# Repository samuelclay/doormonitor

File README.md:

remote-door-sensor
==================

Turns a remote light on and off based on the position of a door.

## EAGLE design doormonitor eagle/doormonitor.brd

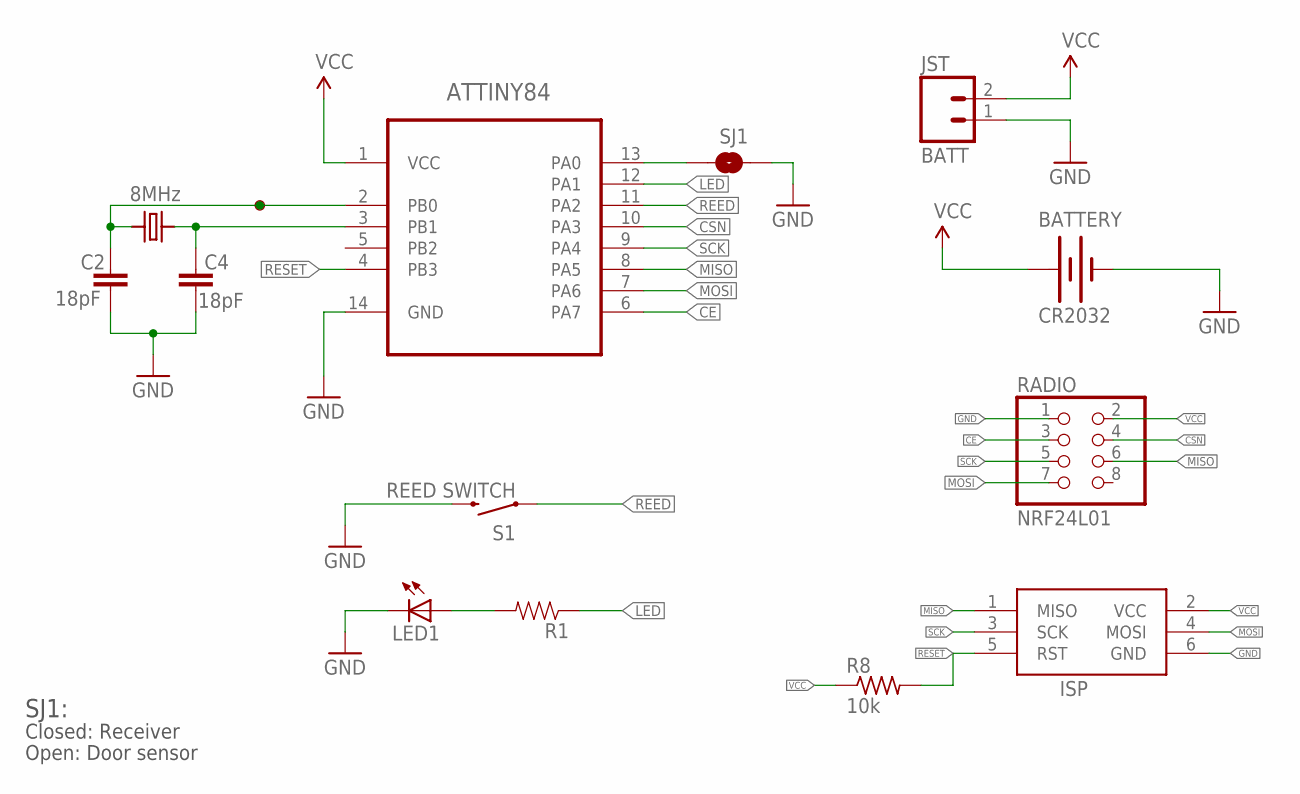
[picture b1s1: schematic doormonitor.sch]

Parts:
ATTINY84: ATTINY84-20SSU; SOIC127P600X175-14N
BATTERY: CR2032; BATTCON_20MM_4LEGS_OVERPASTE
C2, C4: 18pF; 0805
ISP: AVRISP-6; AVRISP
JST: BATT; JST-2-PTH-VERT
LED1: LED5MM
R1: RESISTOR0805-RES; 0805
R8: 10k; R0805
RADIO: NRF24L01; 2X04
S1: REED SWITCH; REED_SWITCH_PTH
SJ1: Receiver?; SJ_2S
U$1: VIA; FANCYVIA
Y1: 8MHz; NX8045GB

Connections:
CE: ATTINY84.6 (PA7), RADIO.3
CSN: ATTINY84.10 (PA3), RADIO.4
GND: ATTINY84.14 (GND), BATTERY.2 (-), C2.2, C4.2, ISP.6 (GND), JST.1, LED1.K (C), RADIO.1, S1.P$2 (2), SJ1.1
LED: ATTINY84.12 (PA1), R1.1
MISO: ATTINY84.8 (PA5), ISP.1 (MISO), RADIO.6
MOSI: ATTINY84.7 (PA6), ISP.4 (MOSI), RADIO.7
unnamed: ATTINY84.13 (PA0), SJ1.2
unnamed: ATTINY84.2 (PB0), C2.1, U$1.VIA, Y1.P$2 (2)
unnamed: ATTINY84.3 (PB1), C4.1, Y1.P$1 (1)
unnamed: LED1.A, R1.2
REED: ATTINY84.11 (PA2), S1.P$1 (1)
RESET: ATTINY84.4 (PB3), ISP.5 (RST), R8.2
SCK: ATTINY84.9 (PA4), ISP.3 (SCK), RADIO.5
VCC: ATTINY84.1 (VCC), BATTERY.1 (+), ISP.2 (VCC), JST.2, R8.1, RADIO.2

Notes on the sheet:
Closed: Receiver
Open: Door sensor
SJ1:

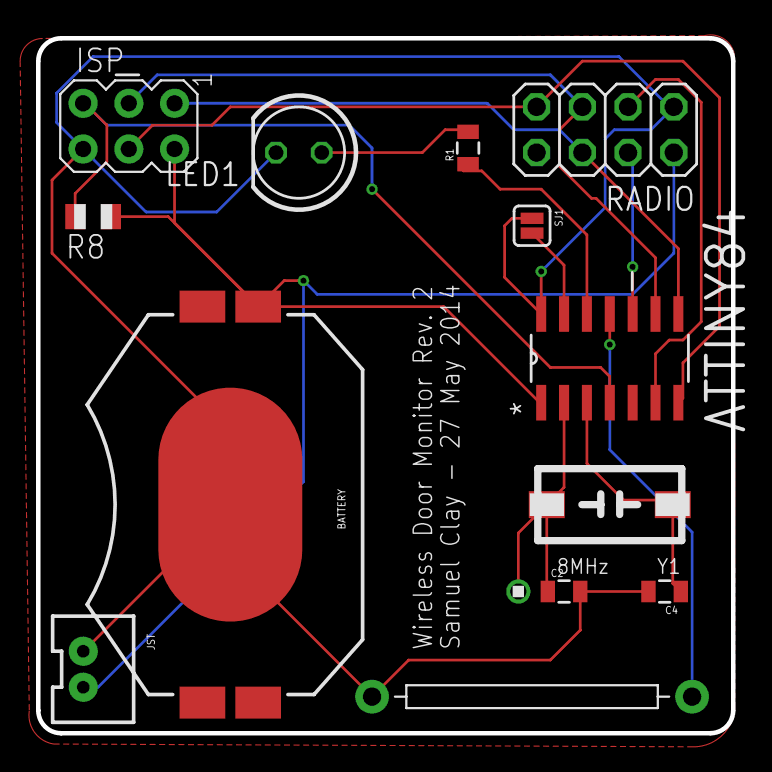
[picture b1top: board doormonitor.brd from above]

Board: 4 copper layers, 38.6 x 38.6 mm, 14 parts (0 on the bottom side), 14 nets.

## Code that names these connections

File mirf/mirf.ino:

/*

This is an attiny84 example code for the nRF24L01 that can communicate with RF24 library

All the support files and libraries for the attiny for nRF24L01 is at repo listed  below

 *  repo   : https://github.com/stanleyseow/arduino-nrf24l01/
 *  Author : Stanley Seow
 *  e-mail : stanleyseow@gmail.com
 *  date   : 8 Aug 2013
 
 Some default values to take note when using this mirf/spi85 library
 Uses Mirf forked library from https://github.com/xdarklight/arduino-nrf24l01
 
 - node addressing is similar to RF24 libs but the bytes are flipped 
 
   byte TADDR[] = {0xe3, 0xf0, 0xf0, 0xf0, 0xf0}; will matches receiver node of RF24 below 
   const uint64_t pipes[2] = { 0x7365727631LL, 0xF0F0F0F0E3LL };
 
 The repo for the RF24 lib is at https://github.com/stanleyseow/RF24/

 Added TinyDebugSerial to the codes for TX only serial debugging
 https://code.google.com/p/arduino-tiny/

*/

#include <SPI85.h>
#include <Mirf.h>
#include <MirfHardwareSpi85Driver.h>
#include <TinyDebugSerial.h>
TinyDebugSerial mySerial = TinyDebugSerial(); // PB0 on attiny84

// This USI was defined in SPI85.cpp
// Not to be confused with SPI (MOSI/MISO) used by ICSP pins
// Refer to page 61 of attiny84 datahseet
//
//#define USI-DO  5
//#define USI-DI  4
//#define USCK   6

#define CE    7    
#define CSN   3 

// ATMEL ATTINY84 / ARDUINO
//
//                           +-\/-+
//                     VCC  1|    |14  GND
//  SerialTx   (D  0)  PB0  2|    |13  AREF (D 10)
//             (D  1)  PB1  3|    |12  PA1  (D  9) 
//  RESET              PB3  4|    |11  PA2  (D  8) 
//  PWM  INT0  (D  2)  PB2  5|    |10  PA3  (D  7)  CE
//  SS/CSN     (D  3)  PA7  6|    |9   PA4  (D  6)  USCK
//  USI-DI     (D  4)  PA6  7|    |8   PA5  (D  5)  USI-DO
//                           +----+

int bufferSize = 0;
char buffer[32] = "";
unsigned int counter = 0; 
uint8_t nodeID = 0;

void setup(){
  
  mySerial.begin( 9600 );    // for tiny_debug_serial 
  
  Mirf.cePin = CE;
  Mirf.csnPin = CSN;
  Mirf.spi = &MirfHardwareSpi85;
  Mirf.init();

  // This address is compatible with my example of rpi-hub or nRF24_Arduino_as_hub
  // at repo https://github.com/stanleyseow/RF24/examples/ 
  
  byte RADDR[] = {0xe7, 0xde, 0xde, 0xde, 0xde};
  byte TADDR[] = {0xe9, 0xde, 0xde, 0xde, 0xde};
 
  // Get nodeID from TXADDR 
  nodeID = *TADDR & 0xff; 
  
  // Compatible with RF24
  Mirf.baseConfig = _BV(EN_CRC) | _BV(CRCO);
  
  // RF_DR_LOW, RF_DR_HIGH
  // 00 - 1Mbps
  // 01 - 2Mbps
  // 10 - 250Kbps
  // 11 - Reserved
  // 1<<2 & 1<<1 is for Max RF Power
  Mirf.configRegister( RF_SETUP,( 1<<RF_DR_LOW | 0<<RF_DR_HIGH ) | 1<<2 | 1<<1 );
  
  Mirf.channel = 0x55; // Same as rpi-hub and sendto_hub ( channel 85 )
  
  Mirf.setRADDR(RADDR);  
  Mirf.setTADDR(TADDR);
  Mirf.config();
  
  // Enable dynamic payload on the other side
  Mirf.configRegister( FEATURE, 1<<EN_DPL ); 
  Mirf.configRegister( DYNPD, 1<<DPL_P0 | 1<<DPL_P1 | 1<<DPL_P2 | 1<<DPL_P3 | 1<<DPL_P4 | 1<<DPL_P5 ); 
  
  delay(100);
  
  // Print out register readinds for important settings
  uint8_t rf_ch, rf_setup = 0;
  byte tx_addr[5];
  byte rx_addr[5];
  
  Mirf.readRegister(RF_CH, &rf_ch,sizeof(rf_ch));
  Mirf.readRegister(RF_SETUP, &rf_setup, sizeof(rf_setup));
  Mirf.readRegister(TX_ADDR, tx_addr, sizeof(tx_addr));
  Mirf.readRegister(RX_ADDR_P1, rx_addr, sizeof(rx_addr));
    
  mySerial.println();
  
  mySerial.print("RF_CH :0x");
  mySerial.println(rf_ch,HEX);  
  
  mySerial.print("RF_SETUP :0x");
  mySerial.println(rf_setup,HEX);  
  
  mySerial.print("TX_ADDR :");
  for ( int i=0;i<5;i++ ) {  // Loop 5 times, print in HEX
  mySerial.print( tx_addr[i], HEX);
  }
  mySerial.println();
  
  mySerial.print("RX_ADDR :");
  for ( int i=0;i<5;i++ ) {  // Loop 5 times, print in HEX
  mySerial.print( rx_addr[i], HEX);
  }
  mySerial.println();
  
  delay(1000);      // For serial debug to read the init config output
}

void loop(){
  
  uint8_t sent = false;
  unsigned long timer1;

  timer1 = millis();
  counter++;

  sprintf(buffer,"%2X,%u,%08lu",nodeID,counter,timer1);
  Mirf.payload = strlen(buffer);

  mySerial.print("Len :");
  mySerial.print(strlen(buffer));
  mySerial.print(" Buffer :");  
  mySerial.println(buffer);
 
  Mirf.send((byte *) buffer);
  
  while( Mirf.isSending() )
  {
    delay(1);
    sent = true; // Sent success
  }
  
  if (sent) {   
        mySerial.print("Sent :");
        mySerial.println(buffer);
    } else {
    }
    
    delay(1000);
} // End loop()

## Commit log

2013-10-18 Adding receiver and sensor.
2013-10-18 Moving from toggle to state.
2013-10-29 Cleaning up source.
2013-10-30 Adding serial port reading for cocoa.
2013-10-30 Moving things around.
2013-11-12 New modules for attiny and mirf library.
2013-11-12 Moving license and readme.
2013-11-12 Removing broken submodules.
2013-11-12 Adding new mirf and rf24 for attiny modules.
2013-11-13 Trying out a sleep on the receiver.
2013-11-14 Beginning branch out for ATMega and ATTiny.
2013-11-16 Adding interrupts and ATMega compatibility.
2013-11-16 Fixing types. The RF24 library f's up half the data. WHY?!
2013-11-18 Cleaning up repo. Archiving mirf and atmega code. Attiny code runs on atmega just fine.
2013-11-19 Renaming ino file.
2014-04-30 Adding eagle files. Needs hookups.
2014-04-30 Board layout. Includes optional JST connector.
2014-05-22 Updating schematic.
2014-05-22 Removing unused line.
2014-05-22 Removing unused board files.
2014-05-27 Moving dirs and trying out a breadboard to diagnose protoboard and pcb.
2014-05-28 Fixing pinchange.
2014-05-28 Adding CAM files and Seeed Studio drill rules.

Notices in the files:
parts and their libraries:
SparkFun-Electromechanical: Licensing: CC v3.0 Share-Alike You are welcome to use this library for commercial purposes.
